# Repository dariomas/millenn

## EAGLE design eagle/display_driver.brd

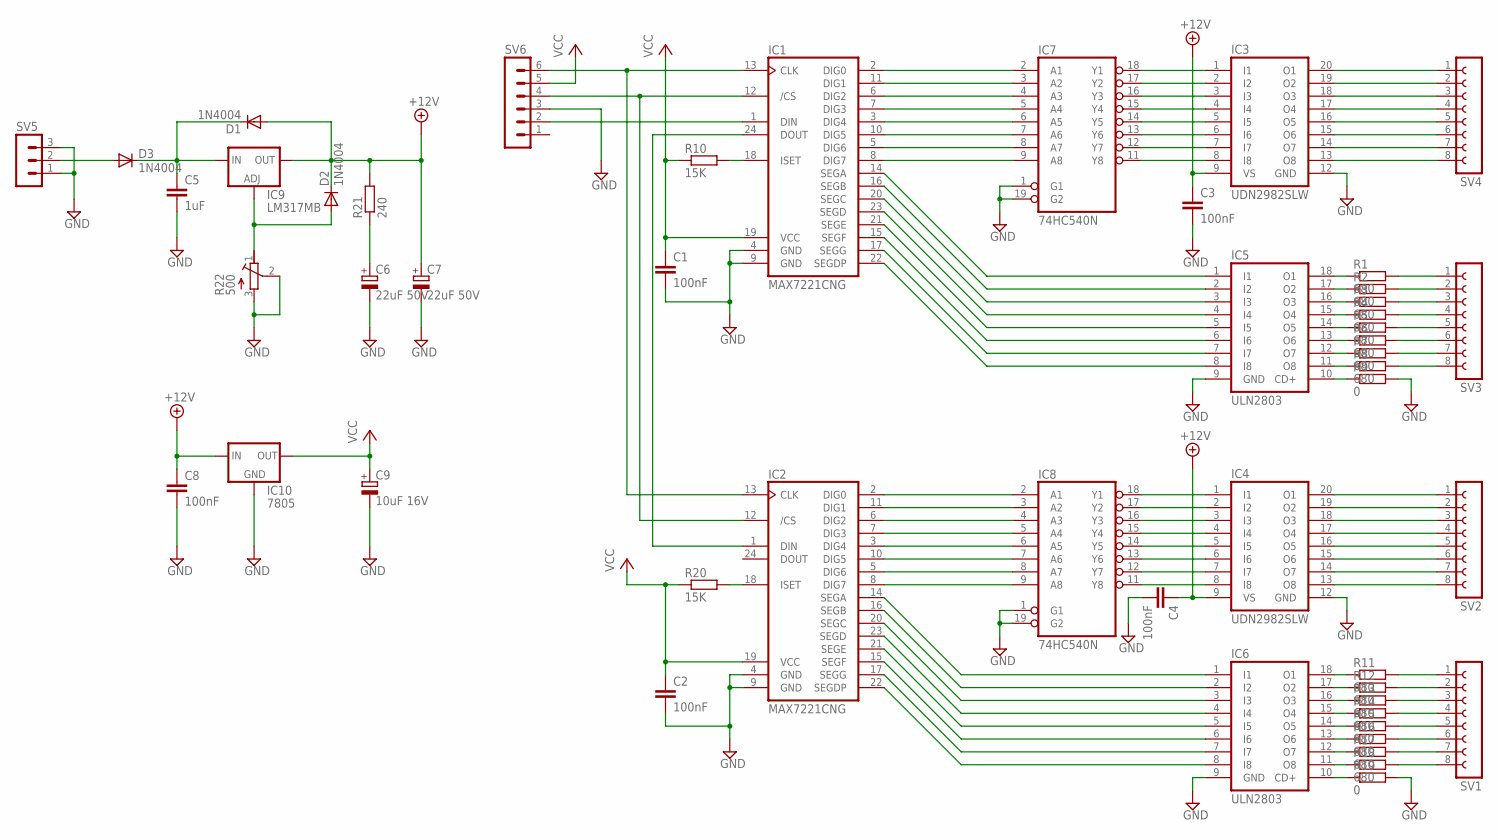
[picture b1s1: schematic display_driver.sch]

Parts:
C1, C2, C3, C4, C8: 100nF; C5B2.5
C5: 1uF; C5B2.5
C6, C7: 22uF 50V; E3,5-8
C9: 10uF 16V; E3,5-8
D1, D2, D3: 1N4004; DO41-10
IC1, IC2: MAX7221CNG; DIL24-3
IC3, IC4: UDN2982SLW; SO20W
IC5, IC6: ULN2803; DIL18
IC7, IC8: 74HC540N; DIL20
IC9: LM317MB; TO220L1
IC10: 7805; 78XXL
R1, R2, R3, R4, R5, R6, R7, R8, R11, R12, R13, R14, R15, R16, R17, R18: 680; 0207/10
R9, R19: 0; 0207/10
R10, R20: 15K; 0207/10
R21: 240; 0207/10
R22: 500; RTRIMT93YA
SV1, SV2, SV3, SV4: FE08-1; FE08
SV5: MA03-1
SV6: MA06-1

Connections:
+12V: C3.1, C4.1, C7.+, C8.1, D1.A, D2.C, IC3.9 (VS), IC4.9 (VS), IC9.2 (OUT), IC10.IN, R21.2
GND: C1.2, C2.2, C3.2, C4.2, C5.2, C6.-, C7.-, C8.2, C9.-, IC1.4 (GND), IC1.9 (GND), IC2.4 (GND), IC2.9 (GND), IC3.12 (GND), IC4.12 (GND), IC5.9 (GND), IC6.9 (GND), IC7.1 (G1), IC7.10 (GND), IC7.19 (G2), IC8.1 (G1), IC8.10 (GND), IC8.19 (G2), IC10.GND, R9.2, R19.2, R22.2 (S), R22.3 (A), SV5.1, SV5.3, SV6.3
unnamed: IC1.2 (DIG0), IC7.2 (A1)
unnamed: IC1.11 (DIG1), IC7.3 (A2)
unnamed: IC1.6 (DIG2), IC7.4 (A3)
unnamed: IC1.7 (DIG3), IC7.5 (A4)
unnamed: IC1.3 (DIG4), IC7.6 (A5)
unnamed: IC1.10 (DIG5), IC7.7 (A6)
unnamed: IC1.5 (DIG6), IC7.8 (A7)
unnamed: IC1.8 (DIG7), IC7.9 (A8)
unnamed: IC3.1 (I1), IC7.18 (Y1)
unnamed: IC3.2 (I2), IC7.17 (Y2)
unnamed: IC3.3 (I3), IC7.16 (Y3)
unnamed: IC3.4 (I4), IC7.15 (Y4)
unnamed: IC3.5 (I5), IC7.14 (Y5)
unnamed: IC3.6 (I6), IC7.13 (Y6)
unnamed: IC3.7 (I7), IC7.12 (Y7)
unnamed: IC3.8 (I8), IC7.11 (Y8)
unnamed: IC1.14 (SEGA), IC5.1 (I1)
unnamed: IC1.16 (SEGB), IC5.2 (I2)
unnamed: IC1.20 (SEGC), IC5.3 (I3)
unnamed: IC1.23 (SEGD), IC5.4 (I4)
unnamed: IC1.21 (SEGE), IC5.5 (I5)
unnamed: IC1.15 (SEGF), IC5.6 (I6)
unnamed: IC1.17 (SEGG), IC5.7 (I7)
unnamed: IC1.22 (SEGDP), IC5.8 (I8)
unnamed: IC5.18 (O1), R1.1
unnamed: IC5.17 (O2), R2.1
unnamed: IC5.16 (O3), R3.1
unnamed: IC3.20 (O1), SV4.1
unnamed: IC3.19 (O2), SV4.2
unnamed: IC3.18 (O3), SV4.3
unnamed: IC3.17 (O4), SV4.4
unnamed: IC3.16 (O5), SV4.5
unnamed: IC3.15 (O6), SV4.6
unnamed: IC3.14 (O7), SV4.7
unnamed: IC5.15 (O4), R4.1
unnamed: IC5.14 (O5), R5.1
unnamed: IC5.13 (O6), R6.1
unnamed: IC5.12 (O7), R7.1
unnamed: IC5.11 (O8), R8.1
unnamed: IC3.13 (O8), SV4.8
unnamed: R1.2, SV3.1
unnamed: R2.2, SV3.2
unnamed: IC5.10 (CD+), R9.1
unnamed: IC1.18 (ISET), R10.2
unnamed: IC1.24 (DOUT), IC2.1 (DIN)
unnamed: IC1.13 (CLK), IC2.13 (CLK), SV6.6
unnamed: IC1.12 (/CS), IC2.12 (/CS), SV6.4
unnamed: IC2.2 (DIG0), IC8.2 (A1)
unnamed: IC2.11 (DIG1), IC8.3 (A2)
unnamed: IC2.6 (DIG2), IC8.4 (A3)
unnamed: IC2.7 (DIG3), IC8.5 (A4)
unnamed: IC2.3 (DIG4), IC8.6 (A5)
unnamed: IC2.10 (DIG5), IC8.7 (A6)
unnamed: IC2.5 (DIG6), IC8.8 (A7)
unnamed: IC2.8 (DIG7), IC8.9 (A8)
unnamed: IC4.1 (I1), IC8.18 (Y1)
unnamed: IC4.2 (I2), IC8.17 (Y2)
unnamed: IC4.3 (I3), IC8.16 (Y3)
unnamed: IC4.4 (I4), IC8.15 (Y4)
unnamed: IC4.5 (I5), IC8.14 (Y5)
unnamed: IC4.6 (I6), IC8.13 (Y6)
unnamed: IC4.7 (I7), IC8.12 (Y7)
unnamed: IC4.8 (I8), IC8.11 (Y8)
unnamed: IC6.10 (CD+), R19.1
unnamed: IC2.14 (SEGA), IC6.1 (I1)
unnamed: IC2.16 (SEGB), IC6.2 (I2)
unnamed: IC2.20 (SEGC), IC6.3 (I3)
unnamed: IC2.23 (SEGD), IC6.4 (I4)
unnamed: IC2.21 (SEGE), IC6.5 (I5)
unnamed: IC2.15 (SEGF), IC6.6 (I6)
unnamed: IC2.17 (SEGG), IC6.7 (I7)
unnamed: IC2.22 (SEGDP), IC6.8 (I8)
unnamed: IC6.11 (O8), R18.1
unnamed: IC6.12 (O7), R17.1
unnamed: IC6.13 (O6), R16.1
unnamed: IC6.14 (O5), R15.1
unnamed: IC6.15 (O4), R14.1
unnamed: IC6.16 (O3), R13.1
unnamed: IC6.17 (O2), R12.1
unnamed: IC6.18 (O1), R11.1
unnamed: IC2.18 (ISET), R20.2
unnamed: C5.1, D1.C, D3.C, IC9.3 (IN)
unnamed: R3.2, SV3.3
unnamed: D2.A, IC9.1 (ADJ), R22.1 (E)
unnamed: R4.2, SV3.4
unnamed: C6.+, R21.1
unnamed: D3.A, SV5.2
unnamed: IC1.1 (DIN), SV6.2
unnamed: R5.2, SV3.5
unnamed: R6.2, SV3.6
unnamed: R7.2, SV3.7
unnamed: R8.2, SV3.8
unnamed: IC4.20 (O1), SV2.1
unnamed: IC4.19 (O2), SV2.2
unnamed: IC4.18 (O3), SV2.3
unnamed: IC4.17 (O4), SV2.4
unnamed: IC4.16 (O5), SV2.5
unnamed: IC4.15 (O6), SV2.6
unnamed: IC4.14 (O7), SV2.7
unnamed: IC4.13 (O8), SV2.8
unnamed: R11.2, SV1.1
unnamed: R12.2, SV1.2
unnamed: R13.2, SV1.3
unnamed: R14.2, SV1.4
unnamed: R15.2, SV1.5
unnamed: R16.2, SV1.6
unnamed: R17.2, SV1.7
unnamed: R18.2, SV1.8
VCC: C1.1, C2.1, C9.+, IC1.19 (VCC), IC2.19 (VCC), IC7.20 (VCC), IC8.20 (VCC), IC10.OUT, R10.1, R20.1, SV6.5

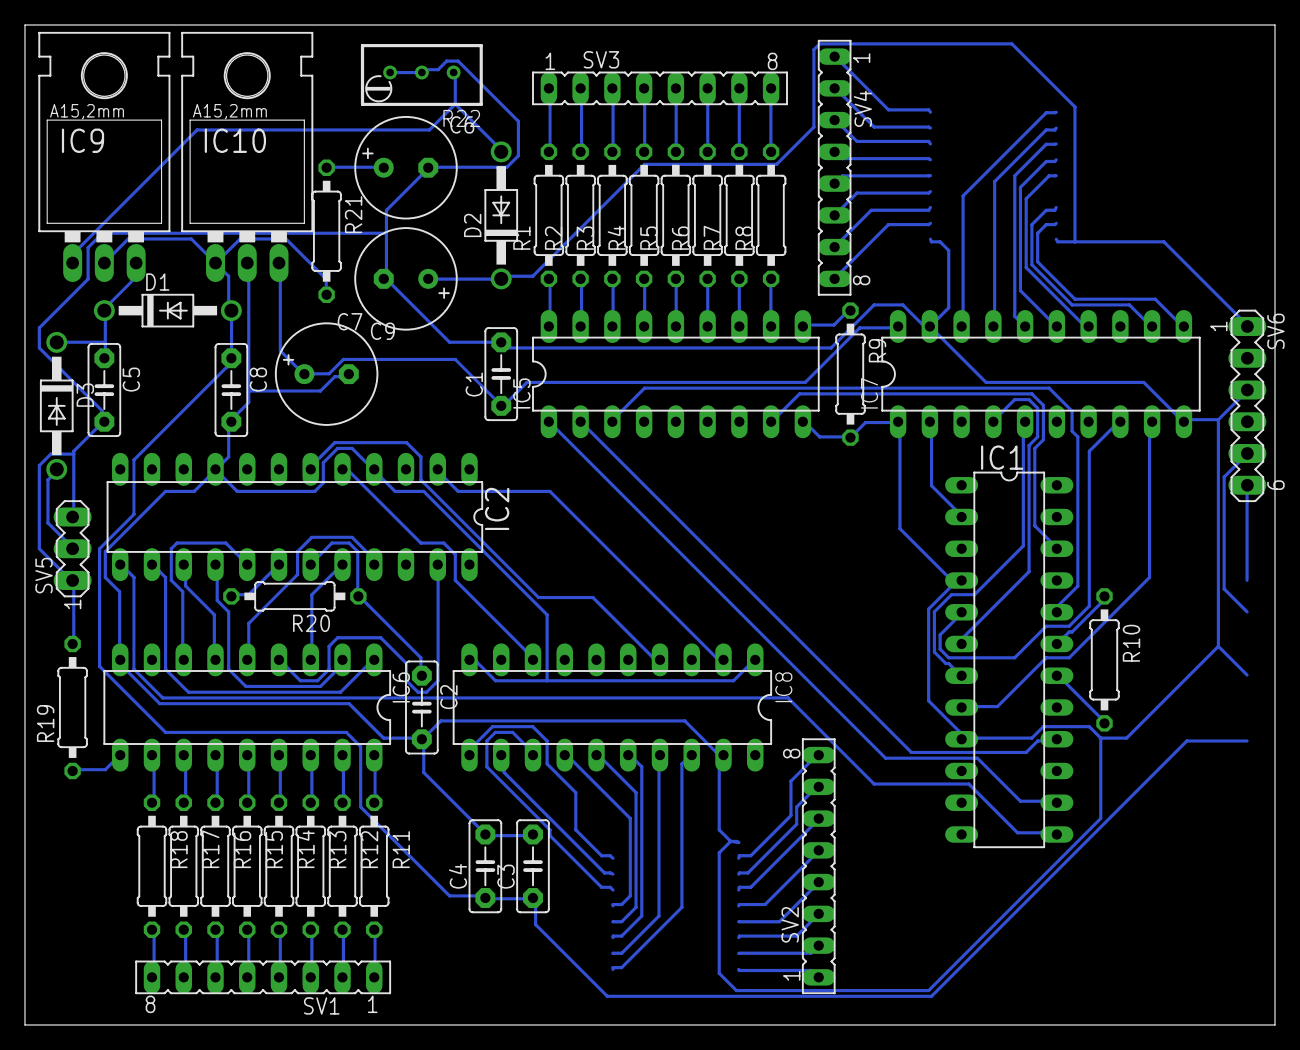
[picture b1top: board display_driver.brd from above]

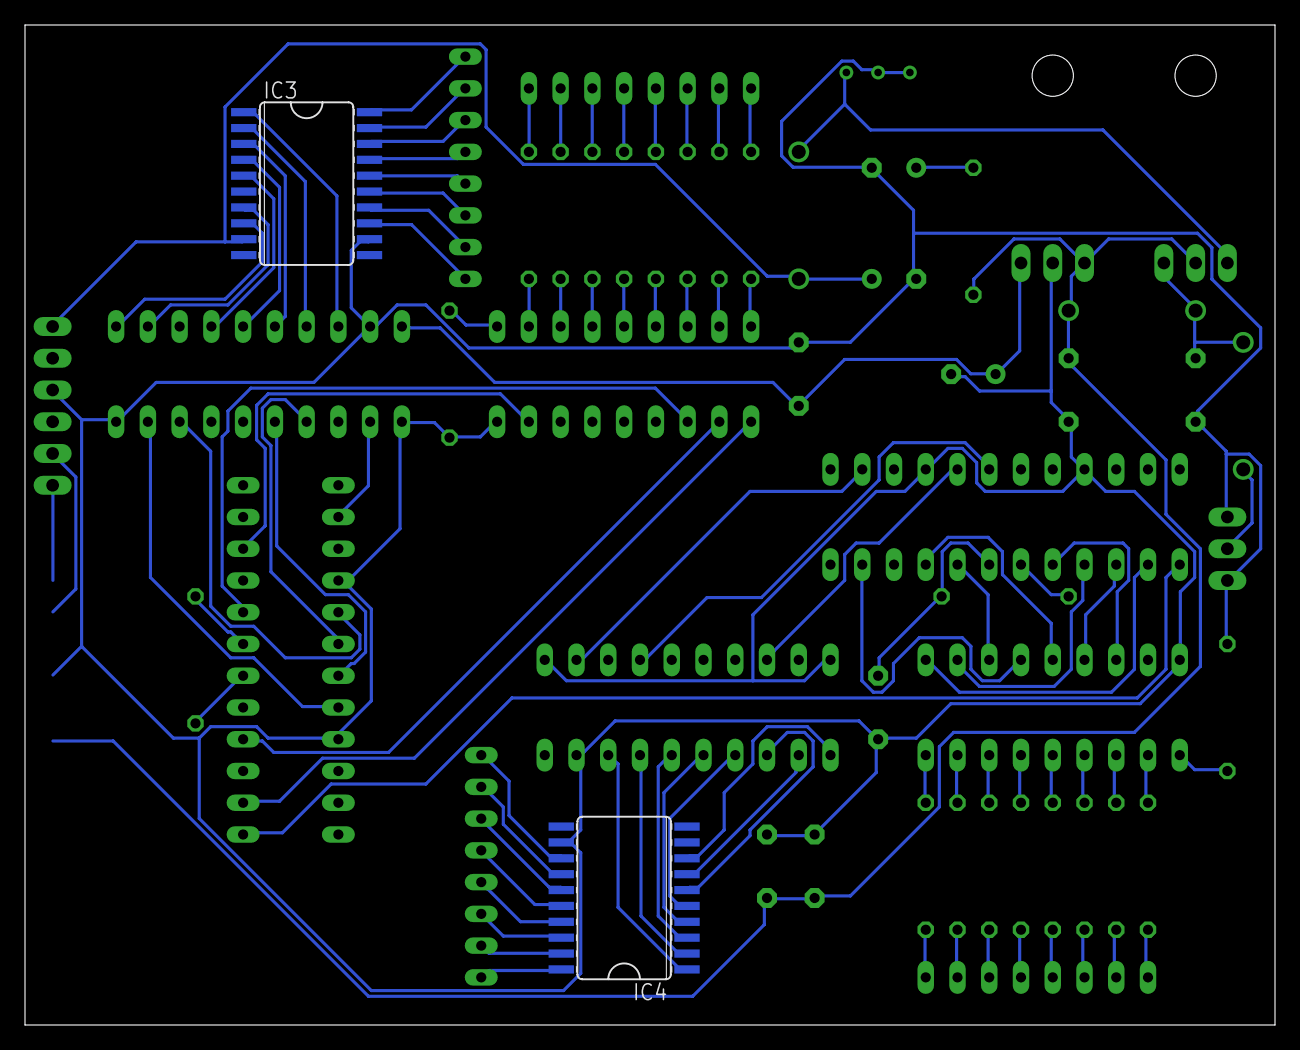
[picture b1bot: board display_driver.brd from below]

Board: 2 copper layers, 100.0 x 80.0 mm, 50 parts (2 on the bottom side), 111 nets.

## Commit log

2020-07-10 Added Arduino sources
2020-07-10 Added Eagle board
